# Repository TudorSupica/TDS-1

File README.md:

The TDS-1 is the first guitar pedal I ever built, and it shows. It's simple design is well suited for amateur and begginer use, since it doesn't require a large number of components.

The reason why I designed and built a distortion pedal as my first pedal instead of something like a fuzz is solely because I found it to be well balanced between difficuly and the "rewarding" feeling you get after building it.

The first version I built is also a bespoke one, a tad bit different to what's presented in the schematic. It does look a bit sketchy, but i promise, it works like a charm. Sadly i forgot to record any demos with it.

https://github.com/user-attachments/assets/b5b1185e-1a2f-4fae-9976-0384d8a1ae87

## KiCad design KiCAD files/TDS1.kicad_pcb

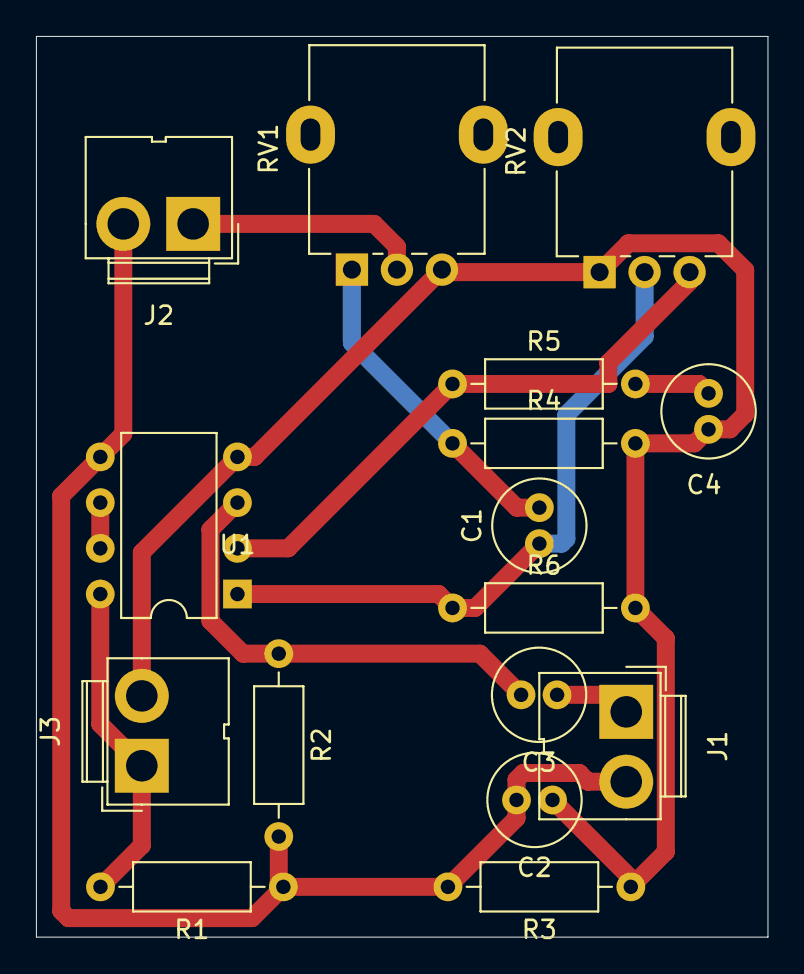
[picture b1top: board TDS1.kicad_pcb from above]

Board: 2 copper layers, 40.6 x 50.0 mm, 16 parts (0 on the bottom side), 11 nets.

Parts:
C1, C2, C3, C4: 10uF; C_Radial_D5.0mm_H11.0mm_P2.00mm
J1, J2, J3: Conn_01x02_Pin; JWT_A3963_1x02_P3.96mm_Vertical
R1, R3, R4: 10k; R_Axial_DIN0207_L6.3mm_D2.5mm_P10.16mm_Horizontal
R2: 100k; R_Axial_DIN0207_L6.3mm_D2.5mm_P10.16mm_Horizontal
R5, R6: 1k; R_Axial_DIN0207_L6.3mm_D2.5mm_P10.16mm_Horizontal
RV1, RV2: 100k; Potentiometer_Alpha_RD901F-40-00D_Single_Vertical
U1: TL072; DIP-8_W7.62mm

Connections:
0: C2.2, J1.2, J2.2, R1.1, R2.2, R3.2, U1.5 (+)
+9V: J3.1, R1.2, U1.8 (V+)
GND: C2.1, C4.1, J3.2, R3.1, R4.2, R6.2, RV1.3, RV2.1, U1.4 (V-)
unnamed: C1.1, R6.1, RV2.2, U1.1
unnamed: C1.2, R4.1, RV1.1
unnamed: C4.2, R5.2
unnamed: C3.1, J1.1
unnamed: J2.1, RV1.2
unnamed: C3.2, R2.1, U1.3 (+)
unnamed: R5.1, RV2.3, U1.2 (-)
unnamed: U1.6 (-), U1.7

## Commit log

2024-06-13 Added the schematic and KiCAD files
    Added the schematic in .pdf and .jpg form. Beside that I added the KiCAD project files as well as the auto-backups.
2024-06-13 backups
2024-06-30 Backup update
2024-07-09 pcb and schematic
2024-11-19 Update
    Honestly idk
